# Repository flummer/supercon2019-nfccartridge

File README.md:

# NFC Cardtridge for the 2019 Hackaday Superconference Badge

This is a cartridge that provides an NFC tag using an ST25DV. In addition to the RF interface, that can be used without plugging in the cartridge, the ST25DV also have an I2C interface, that is connected to the IO pins on the badge connector, allowing the badge to access the same memory in the NFC tag chip.

This cartridge is based on the [unofficial Superconference 2019 Badge Cartridge template](https://github.com/flummer/supercon2019-cartridgetemplate) and hence include the w25q128 SPI flash and a 100nF cap in addition to the 2x20 pin angled male pin header for the badge connection. The flash allows badge configurations and firmware specific to this cartridge to be loaded from the cartridge it self making it selfcontained.

## Version 1.2 update

This updated version fixes an error in the pin connections on the cartridge connector (the two columns was flipped for some signals).

## Special note about the original version

If you want to use a PCB based on the original version with incorrect connections, it is possible to make a hardware hack on the 20x2 angeled header, where you move the pins around and bend some of them a bit, very precisely.

## License

The contents of this repository is released under the following licence:

 * the "Creative Commons Attribution-ShareAlike 4.0 International License"
   (CC BY-SA 4.0) full text of this license is included in the LICENSE file
   and a copy can also be found at
   http://creativecommons.org/licenses/by-sa/4.0/

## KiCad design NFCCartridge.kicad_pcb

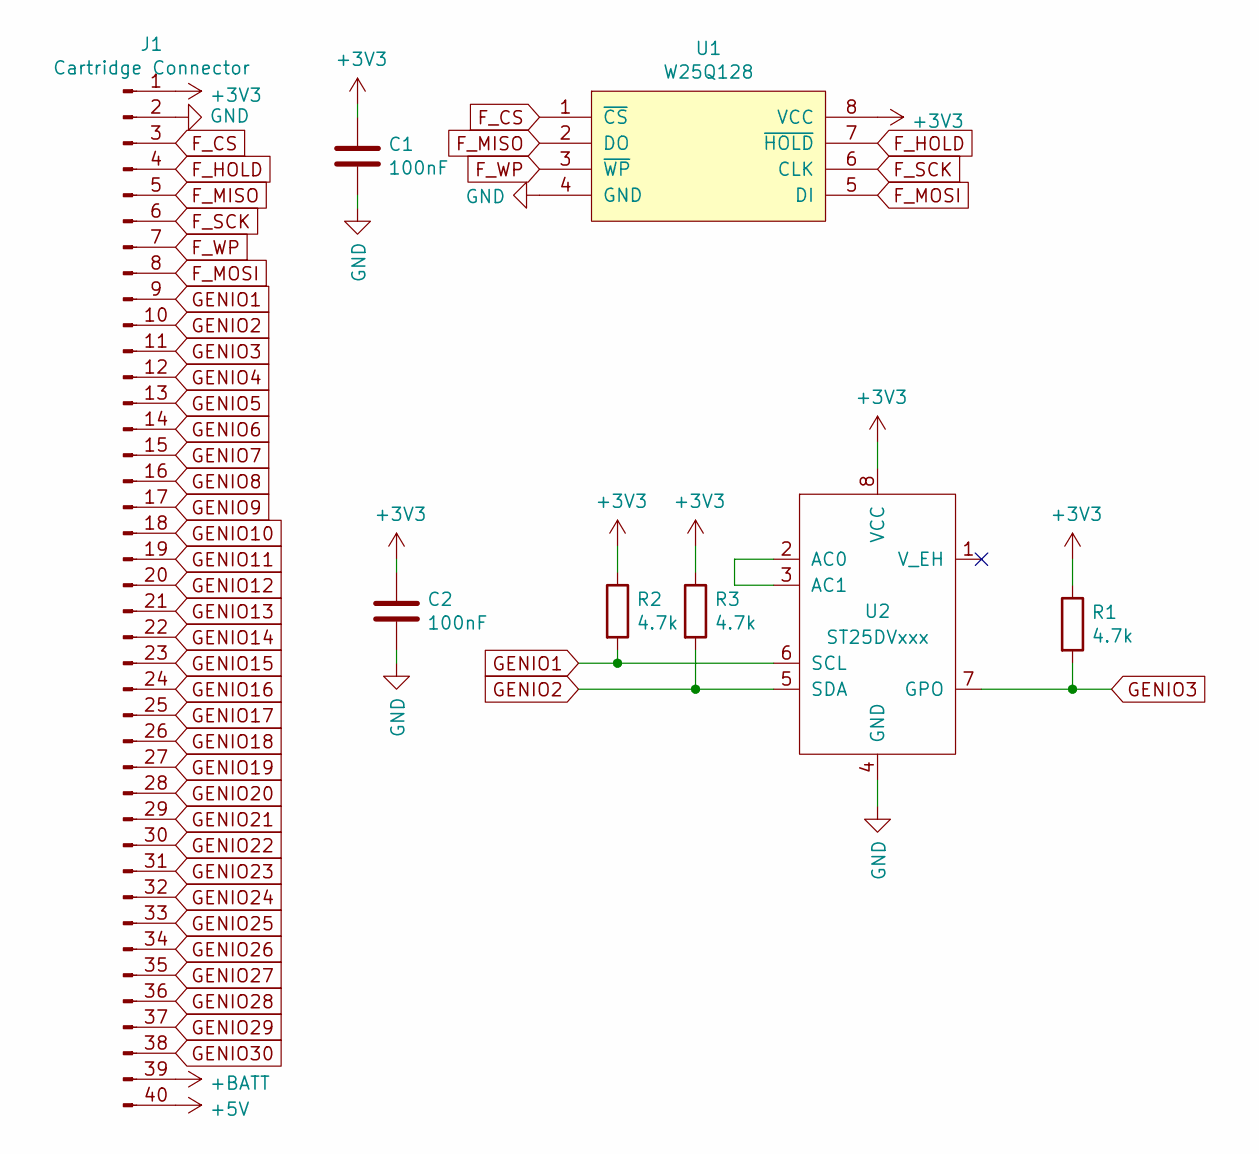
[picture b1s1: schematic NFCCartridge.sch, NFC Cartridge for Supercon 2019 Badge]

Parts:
C1, C2: 100nF; C_0805_HandSoldering
J1: Cartridge Connector; Supercon_Cartridge_40pin_Connector
R1, R2, R3: 4.7k; R_0805_HandSoldering
U1: W25Q128; SO-8_5.3x6.2mm_Pitch1.27mm
U2: ST25DVxxx; SOIC-8_3.9x4.9mm_Pitch1.27mm

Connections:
+3V3: C1.1, C2.1, J1.1, R1.1, R2.1, R3.1, U1.8 (VCC), U2.8 (VCC)
+5V: J1.40
+BATT: J1.39
F_CS: J1.3, U1.1 (~CS)
F_HOLD: J1.4, U1.7 (~HOLD)
F_MISO: J1.5, U1.2 (DO)
F_MOSI: J1.8, U1.5 (DI)
F_SCK: J1.6, U1.6 (CLK)
F_WP: J1.7, U1.3 (~WP)
GENIO1: J1.9, R2.2, U2.6 (SCL)
GENIO2: J1.10, R3.2, U2.5 (SDA)
GENIO3: J1.11, R1.2, U2.7 (GPO)
GENIO4: J1.12
GENIO5: J1.13
GENIO6: J1.14
GENIO7: J1.15
GENIO8: J1.16
GENIO9: J1.17
GENIO10: J1.18
GENIO11: J1.19
GENIO12: J1.20
GENIO13: J1.21
GENIO14: J1.22
GENIO15: J1.23
GENIO16: J1.24
GENIO17: J1.25
GENIO18: J1.26
GENIO19: J1.27
GENIO20: J1.28
GENIO21: J1.29
GENIO22: J1.30
GENIO23: J1.31
GENIO24: J1.32
GENIO25: J1.33
GENIO26: J1.34
GENIO27: J1.35
GENIO28: J1.36
GENIO29: J1.37
GENIO30: J1.38
GND: C1.2, C2.2, J1.2, U1.4 (GND), U2.4 (GND)
unnamed: U2.2 (AC0), U2.3 (AC1)

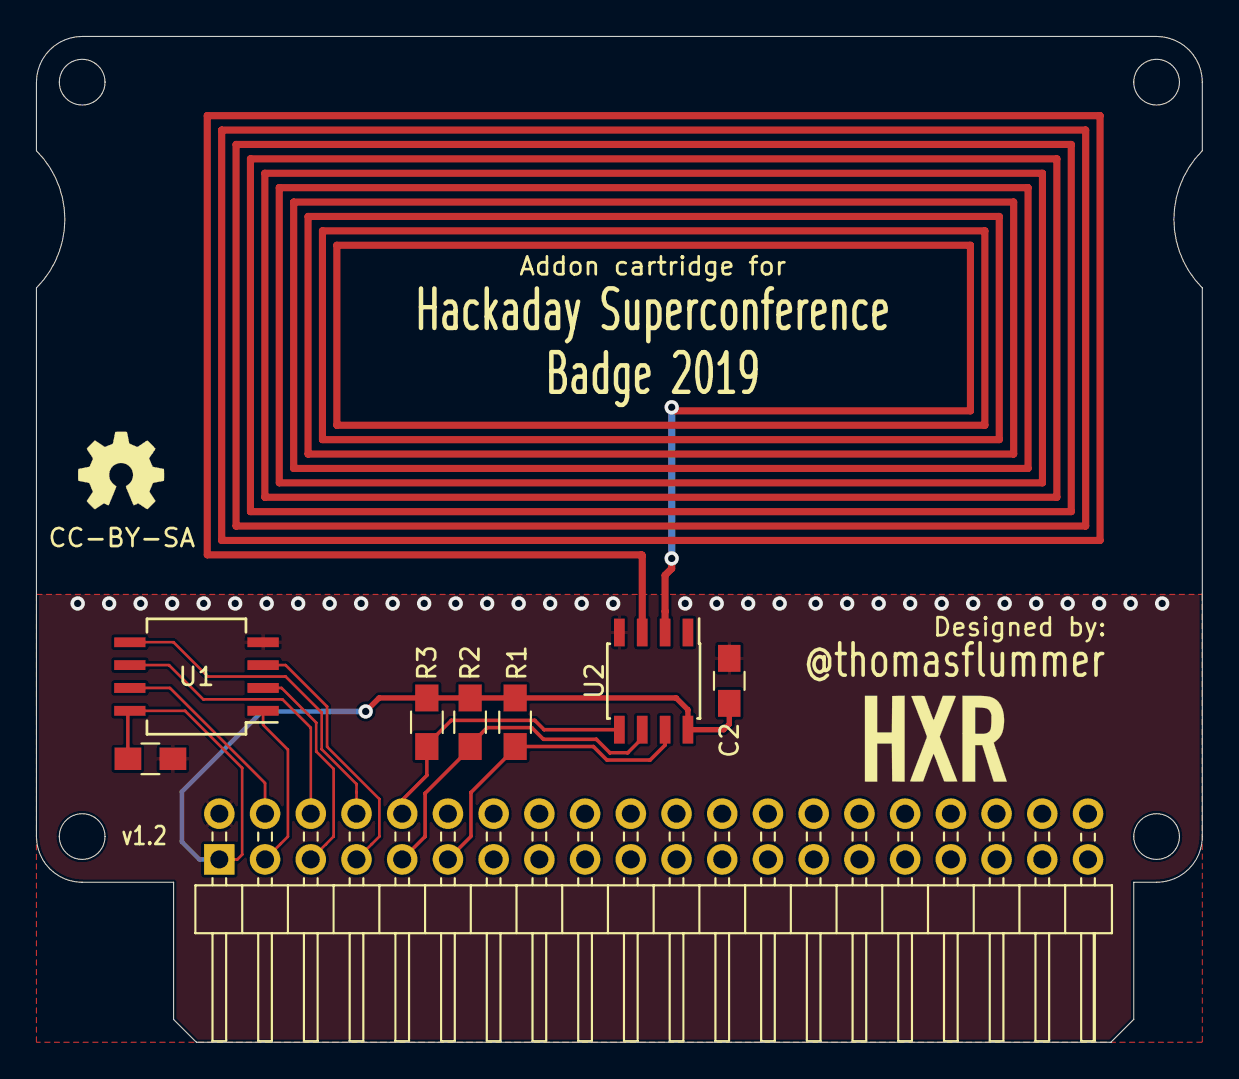
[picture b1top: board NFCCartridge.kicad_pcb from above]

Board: 2 copper layers, 64.8 x 55.9 mm, 8 parts (0 on the bottom side), 12 nets.

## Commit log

2019-10-29 First design of the NFC Cartridge
2019-11-16 Fixed error in cartridge connector pin assignments
    Updated to version 1.2
